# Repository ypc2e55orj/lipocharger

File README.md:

# Li-Po Charger

小容量リポバッテリー充電器

## 仕様

- 電源入力 (5V)
    - USB Type-C
    - 2.54mm ピンヘッダ
- 充電電圧・電流 (1個あたり)
    - 4.2V / 50mA

USB Type-Cとピンヘッダから同時に入力された場合、ピンヘッダからの入力を優先する

充電中赤色LED点灯、充電完了時に消灯

## 部品リスト

|概説|メーカー|型番|個数|
|:-:|:-:|:-:|:-:|
|USB Type-Cコネクタ|Korean Hroparts Elec|TYPE-C-31-M-12|1|
|ZHコネクタ|JST|B2B-ZR-3.4(LF)(SN)|4|
|2.54mmピッチ ピンヘッダ 2P|||1|
|リセッタブルヒューズ|Bourns|MF-NSMF050-2|1|
|ショットキーバリアダイオード|東芝セミコンダクター|CUHS20S60|2|
|Pch MOS-FET|International Rectifier|IRLML6402|1|
|青色LED|OptoSupply|OSBL1608C1A|1|
|黄色LED|OptoSupply|OSYL1608C1A|1|
|赤色LED|OptoSupply|OSHR1608C1A|4|
|積層セラミックコンデンサ|muRata|GRM188R71E105KA12|4|
|薄膜抵抗器 5.1kΩ|Panasonic|ERA-3AED512V|2|
|薄膜抵抗器 430Ω|Panasonic|ERA-3AED431V|1|
|薄膜抵抗器 1kΩ|Panasonic|ERA-3AED102V|1|
|薄膜抵抗器 680Ω|Panasonic|ERA-3AED681V|5|
|薄膜抵抗器 20kΩ|Panasonic|ERA-3AED203V|4|
|Li-Ion充電管理IC|Analog Devices|LTC4054XES5-4.2|4|

## LICENSE

The MIT License

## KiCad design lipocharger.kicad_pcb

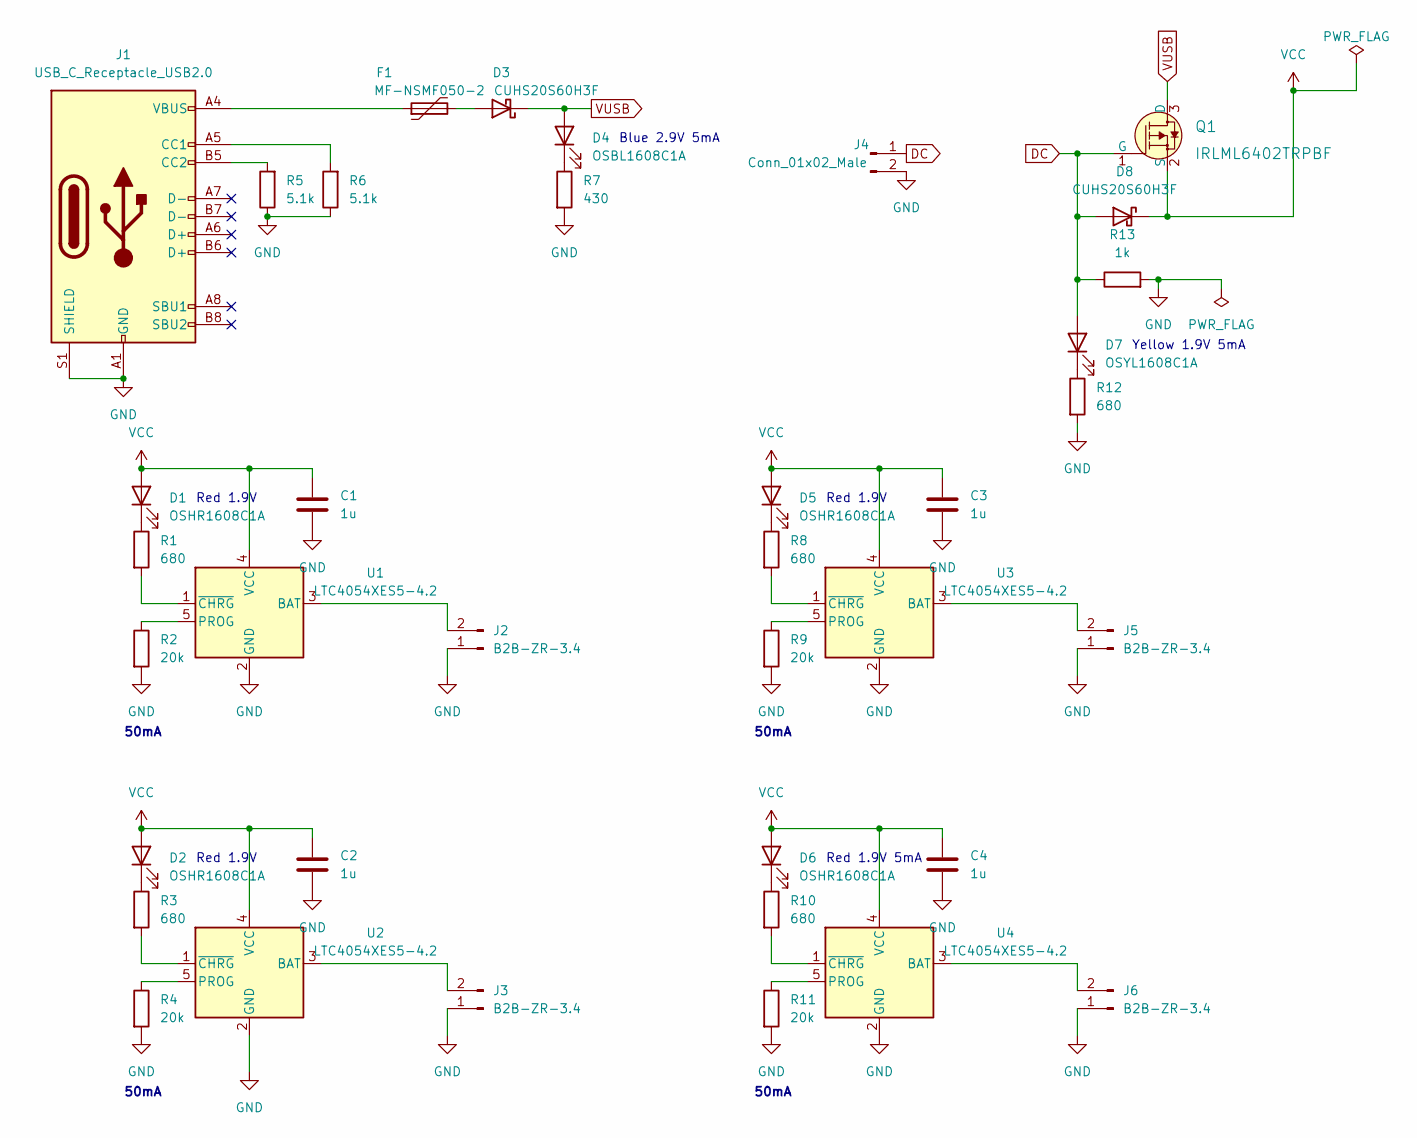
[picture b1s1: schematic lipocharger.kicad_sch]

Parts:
C1, C2, C3, C4: 1u; C_0603_1608Metric
D1, D2, D5, D6: OSHR1608C1A; C_0603_1608Metric
D3, D8: CUHS20S60H3F; US2H
D4: OSBL1608C1A; C_0603_1608Metric
D7: OSYL1608C1A; C_0603_1608Metric
F1: MF-NSMF050-2; Fuse_1206_3216Metric
J1: USB_C_Receptacle_USB2.0; USB_C_Receptacle_HRO_TYPE-C-31-M-12
J2, J3, J5, J6: B2B-ZR-3.4; JST_ZH-1x2
J4: Conn_01x02_Male; PinHeader_1x02_P2.54mm_Vertical
Q1: IRLML6402TRPBF; SOT-23-3; MPN IRLML6402TRPBF; Digi-Key_PN IRLML6402PBFCT-ND
R1, R3, R8, R10, R12: 680; R_0603_1608Metric
R2, R4, R9, R11: 20k; R_0603_1608Metric
R5, R6: 5.1k; R_0603_1608Metric
R7: 430; R_0603_1608Metric
R13: 1k; R_0603_1608Metric
U1, U2, U3, U4: LTC4054XES5-4.2; TSOT-23-5

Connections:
DC: D7.2 (A), D8.2 (A), J4.1, Q1.1 (G), R13.1
GND: C1.2, C2.2, C3.2, C4.2, J1.A1 (GND), J1.A12 (GND), J1.B1 (GND), J1.B12 (GND), J1.S1 (SHIELD), J2.1, J3.1, J4.2, J5.1, J6.1, R2.2, R4.2, R5.1, R6.1, R7.2, R9.2, R11.2, R12.2, R13.2, U1.2 (GND), U2.2 (GND), U3.2 (GND), U4.2 (GND)
unnamed: D1.1 (K), R1.1
unnamed: D2.1 (K), R3.1
unnamed: D3.2 (A), F1.2
unnamed: D4.1 (K), R7.1
unnamed: D5.1 (K), R8.1
unnamed: D6.1 (K), R10.1
unnamed: D7.1 (K), R12.1
unnamed: F1.1, J1.A4 (VBUS), J1.A9 (VBUS), J1.B4 (VBUS), J1.B9 (VBUS)
unnamed: J1.A5 (CC1), R6.2
unnamed: J1.B5 (CC2), R5.2
unnamed: J2.2, U1.3 (BAT)
unnamed: J3.2, U2.3 (BAT)
unnamed: J5.2, U3.3 (BAT)
unnamed: J6.2, U4.3 (BAT)
unnamed: R1.2, U1.1 (~CHRG)
unnamed: R2.1, U1.5 (PROG)
unnamed: R3.2, U2.1 (~CHRG)
unnamed: R4.1, U2.5 (PROG)
unnamed: R8.2, U3.1 (~CHRG)
unnamed: R9.1, U3.5 (PROG)
unnamed: R10.2, U4.1 (~CHRG)
unnamed: R11.1, U4.5 (PROG)
VCC: C1.1, C2.1, C3.1, C4.1, D1.2 (A), D2.2 (A), D5.2 (A), D6.2 (A), D8.1 (K), Q1.2 (S), U1.4 (VCC), U2.4 (VCC), U3.4 (VCC), U4.4 (VCC)
VUSB: D3.1 (K), D4.2 (A), Q1.3 (D)

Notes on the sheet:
50mA
Red 1.9V
Yellow 1.9V 5mA
Red 1.9V 5mA
Blue 2.9V 5mA

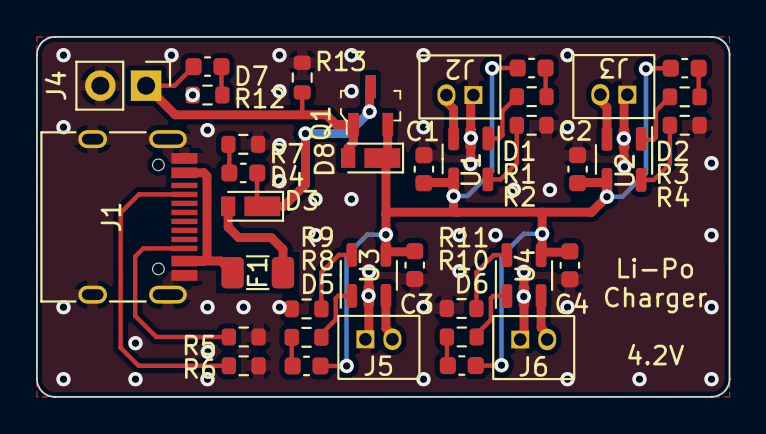
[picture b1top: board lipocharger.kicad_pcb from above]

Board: 2 copper layers, 38.5 x 20.0 mm, 37 parts (0 on the bottom side), 26 nets.

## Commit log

2022-09-18 Add README.md
2022-09-18 Add LICENSE
2022-09-18 Remove LICENSE
2022-09-18 Add voltage specification
2022-09-18 Fix typo
2022-09-18 Add sample image
2022-09-18 Add artwork image
2022-10-03 Add circuit image
